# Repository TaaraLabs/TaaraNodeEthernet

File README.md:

TaaraNode Ethernet
==================

Compact Arduino/JeeNode compatible microcontroller board with on-board Ethernet and RFM12b radio

[WebSite](https://taaralabs.eu/en1)

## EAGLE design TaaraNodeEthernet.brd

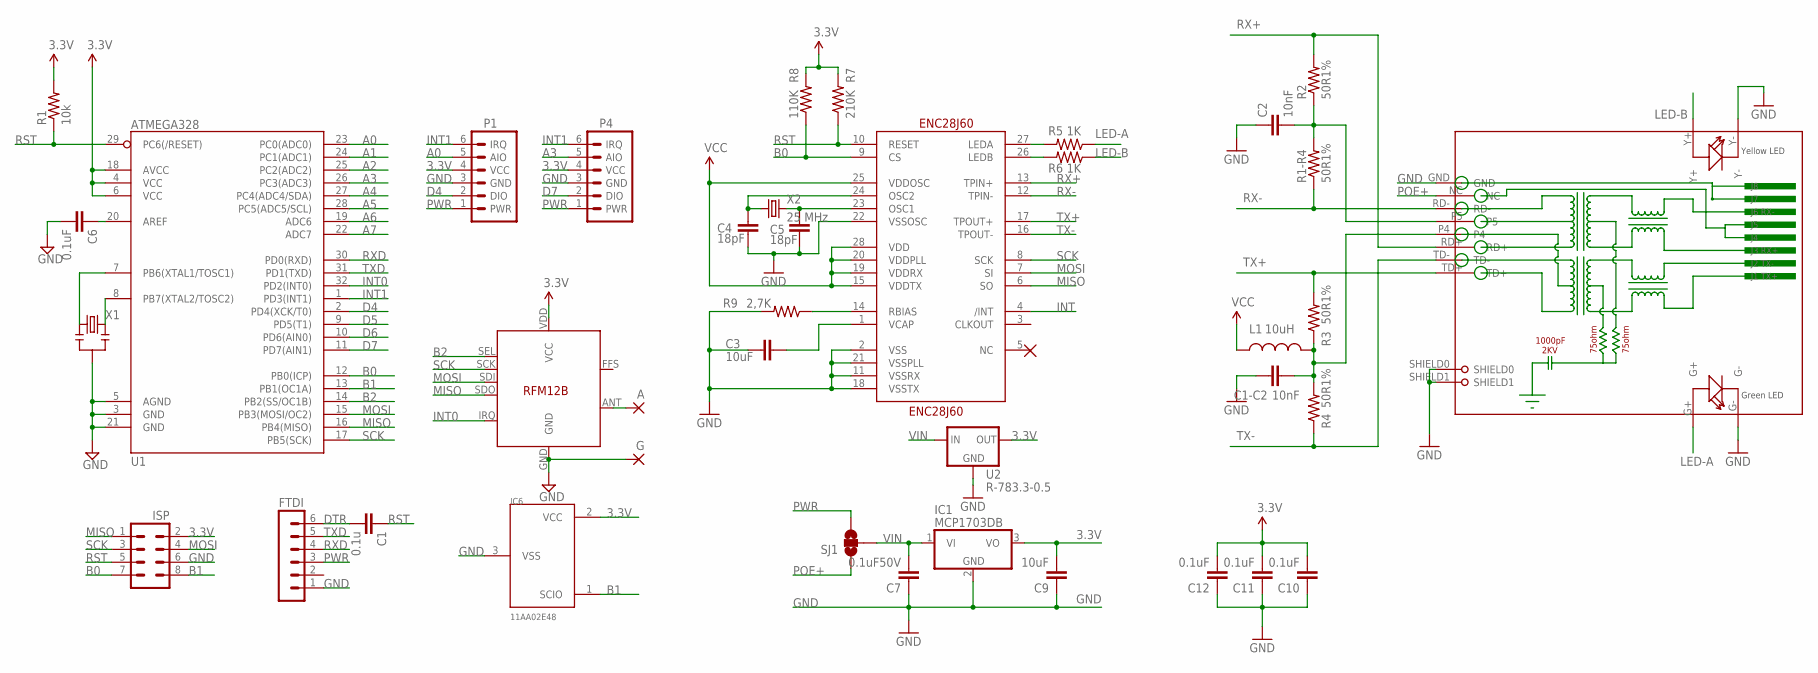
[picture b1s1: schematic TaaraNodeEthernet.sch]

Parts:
A: 1,6/0,8
C1: 0.1u; 0603-CAP
C1-C2, C2: 10nF; 0603-CAP
C3, C9: 10uF; 0603-CAP
C4, C5: 18pF; 0603-CAP
C6, C10, C11, C12: 0.1uF; 0603-CAP
C7: 0.1uF50V; 0603-CAP
ENC28J60: ENC28J60; SSOP28DB
FTDI: MA06-1
G: 1,6/0,8
IC1: MCP1703DB; SOT223
IC6: 11AA02E48; SOT23
L1: 10uH; 0603
P1, P4: JEEPORT-FEMALE; 1X06_FEMALE_LOCK.010
R1: 10k; 0603-RES
R1-R4, R2, R3, R4: 50R1%; 0603-RES
R5, R6: 1K; 0603-RES
R7: 210K; 0603-RES
R8: 110K; 0603-RES
R9: 2,7K; 0603-RES
RJ1: HLJ-6115ANL; HR911105A
SJ1: SOLDERJUMPER_2WAYT; SJ_2
SV7: ISP; MA04-2
U1: ATMEGA328; TQFP32-08
U2: R-783.3-0.5; R-78XX
U$1: RFM12B
X1: RESONATORSMD; RESONATOR-SMD
X2: 25 MHz; CRYSTAL-SMD-3.2X2.5

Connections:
3.3V: C9.2, C10.2, C11.2, C12.2, ENC28J60.15 (VDDTX), ENC28J60.19 (VDDRX), ENC28J60.20 (VDDPLL), ENC28J60.25 (VDDOSC), ENC28J60.28 (VDD), IC1.3 (VO), IC6.2 (VCC), L1.1, P1.4 (VCC), P4.4 (VCC), R1.2, R7.2, R8.2, SV7.2, U1.4 (VCC), U1.6 (VCC), U1.18 (AVCC), U2.OUT, U$1.VDD (VCC)
A0: P1.5 (AIO), U1.23 (PC0(ADC0))
A1: U1.24 (PC1(ADC1))
A2: U1.25 (PC2(ADC2))
A3: P4.5 (AIO), U1.26 (PC3(ADC3))
A4: U1.27 (PC4(ADC4/SDA))
A5: U1.28 (PC5(ADC5/SCL))
A6: U1.19 (ADC6)
A7: U1.22 (ADC7)
B0: ENC28J60.9 (CS), R8.1, SV7.7, U1.12 (PB0(ICP))
B1: IC6.1 (SCIO), SV7.8, U1.13 (PB1(OC1A))
B2: U1.14 (PB2(SS/OC1B)), U$1.SEL
D4: P1.2 (DIO), U1.2 (PD4(XCK/T0))
D5: U1.9 (PD5(T1))
D6: U1.10 (PD6(AIN0))
D7: P4.2 (DIO), U1.11 (PD7(AIN1))
DTR: C1.2, FTDI.6
GND: C1-C2.1, C2.1, C3.1, C4.1, C5.1, C6.2, C7.1, C9.1, C10.1, C11.1, C12.1, ENC28J60.2 (VSS), ENC28J60.11 (VSSRX), ENC28J60.18 (VSSTX), ENC28J60.21 (VSSPLL), ENC28J60.22 (VSSOSC), FTDI.1, G.1, IC1.2 (GND), IC6.3 (VSS), P1.3 (GND), P4.3 (GND), R9.2, RJ1.G-, RJ1.GND, RJ1.SHIELD0, RJ1.SHIELD1, RJ1.Y-, SV7.6, U1.3 (GND), U1.5 (AGND), U1.21 (GND), U2.GND, U$1.GND, X1.2
INT: ENC28J60.4 (/INT)
INT0: U1.32 (PD2(INT0)), U$1.IRQ
INT1: P1.6 (IRQ), P4.6 (IRQ), U1.1 (PD3(INT1))
LED-A: R5.1, RJ1.G+
LED-B: R6.1, RJ1.Y+
MISO: ENC28J60.6 (SO), SV7.1, U1.16 (PB4(MISO)), U$1.SDO
MOSI: ENC28J60.7 (SI), SV7.4, U1.15 (PB3(MOSI/OC2)), U$1.SDI
unnamed: U1.7 (PB6(XTAL1/TOSC1)), X1.1
unnamed: C6.1, U1.20 (AREF)
unnamed: ENC28J60.27 (LEDA), R5.2
unnamed: ENC28J60.26 (LEDB), R6.2
unnamed: ENC28J60.14 (RBIAS), R9.1
unnamed: C3.2, ENC28J60.1 (VCAP)
unnamed: C4.2, ENC28J60.24 (OSC2), X2.1
unnamed: C5.2, ENC28J60.23 (OSC1), X2.3 (2)
unnamed: A.1, U$1.ANT
unnamed: U1.8 (PB7(XTAL2/TOSC2)), X1.3
POE+: RJ1.NC, SJ1.1
PWR: FTDI.3, P1.1 (PWR), P4.1 (PWR), SJ1.3
RCT: C2.2, R1-R4.2, R2.1, RJ1.P5
RST: C1.1, ENC28J60.10 (RESET), R1.1, R7.1, SV7.5, U1.29 (PC6(/RESET))
RX+: ENC28J60.13 (TPIN+), R2.2, RJ1.RD+
RX-: ENC28J60.12 (TPIN-), R1-R4.1, RJ1.RD-
RXD: FTDI.4, U1.30 (PD0(RXD))
SCK: ENC28J60.8 (SCK), SV7.3, U1.17 (PB5(SCK)), U$1.SCK
TCT: C1-C2.2, L1.2, R3.1, R4.2, RJ1.P4
TX+: ENC28J60.17 (TPOUT+), R3.2, RJ1.TD+
TX-: ENC28J60.16 (TPOUT-), R4.1, RJ1.TD-
TXD: FTDI.5, U1.31 (PD1(TXD))
VIN: C7.2, IC1.1 (VI), SJ1.2, U2.IN

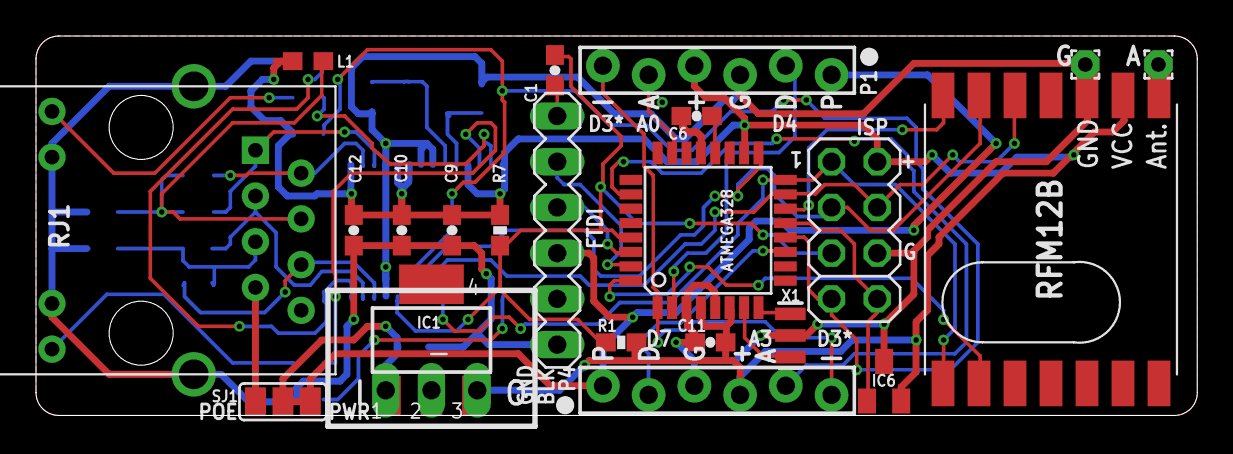
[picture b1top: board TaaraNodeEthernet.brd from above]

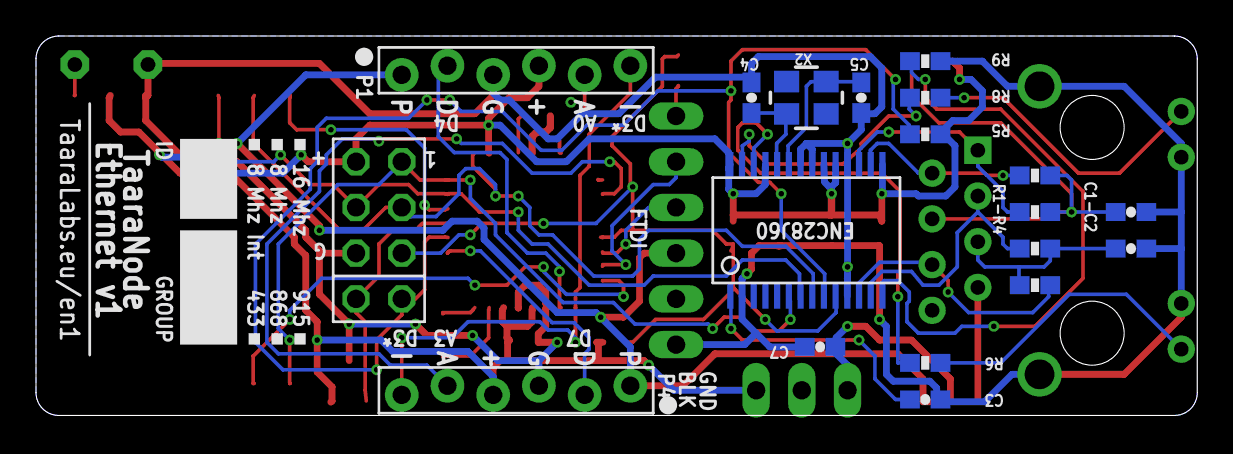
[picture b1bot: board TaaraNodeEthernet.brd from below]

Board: 2 copper layers, 64.5 x 21.1 mm, 40 parts (16 on the bottom side), 39 nets.

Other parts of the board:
U$2: NODEPARAMS

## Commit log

2015-01-22 :lollipop: Added .gitattributes & .gitignore files
2015-01-22 TaaraNodeEthernet
